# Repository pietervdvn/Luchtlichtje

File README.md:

# Luchtlichtje

Source code and hardware spec of the ESP8266 driven Air Quality Indicator "Luchtlichtje" (Dutch for 'air light')

A small ESP/Arduino Project, showing lights indicating the air quality, based on data from luftdaten.info

## API

Get your sensor data at http://api.luftdaten.info/v1/sensor/7245/

## Bill of Materials

- A Luchtlichtje PCB
- 4 LEDS of each colour (RED, YELLOW, GREEN) of 5mm (or some other colours)
- 3 resistors of around 10ohm (use higher such as 220ohm for less brightness)
- 1 photoresistor of a pretty high resistance, in combination with a 1Mohm resistor*

*If you don't like the brightness settings or have a different photoresistor, you can change the code to have other settings*

## Flashing a Luchtlichtje

- Install platformio
- Open the console
- cd to the desired directory (v0.2/firmware)
- `sudo platformio run --target upload`
- Use `platformio run --target monitor` to see what is happening

## Assembly instructions

- Start with placing the resistors. The resistor 'R1 Different'-resistor (bottom right) takes the 1-mega-ohm resistor
- The other three have 10-ohm resistors (upper and left side).
- Next, place the leds. Be carefull, they have to be oriented correctly: the flattened sides go in the middle. Green leds down, red leds up - just like traffic lights. Solder them neatly and straight.
- Place and solder the header pins on the backside of the board.
- Flash the software on the nodemcu and place it on the backside (see above).
- Gently break the board along the cutlines on the right. If they don't come off, use a knife on the back side of the board.
- These small rectangular break-off pieces can be slided in the main board, to place it on your desk.
- The break-off parts easily fall of the board when lifted. To prevent this, place a piece of wire through the holes in the break-off part and the main board.
- All done! Enjoy your Luchtlichtje.

## Troubleshooting

When booting, the board will test all leds blinking from up to down.
If a led does not blink, check the soldering.
If more then the desired leds burn, some LEDS are soldered in the wrong direction.

If the orange leds start blinking one after another; the board is connecting to the wifi. This will always happen for a few seconds when booting.

If the reds leds are blinking, either luftdaten or your sensor is down. 

## Versions

The first version (v1.0) is dated 2018-05-15
The second version (v2.0) is dated 2018-08-24. Changes are: removal of unused transistors, addition of a brightness sensor, fancier placement of resistors.

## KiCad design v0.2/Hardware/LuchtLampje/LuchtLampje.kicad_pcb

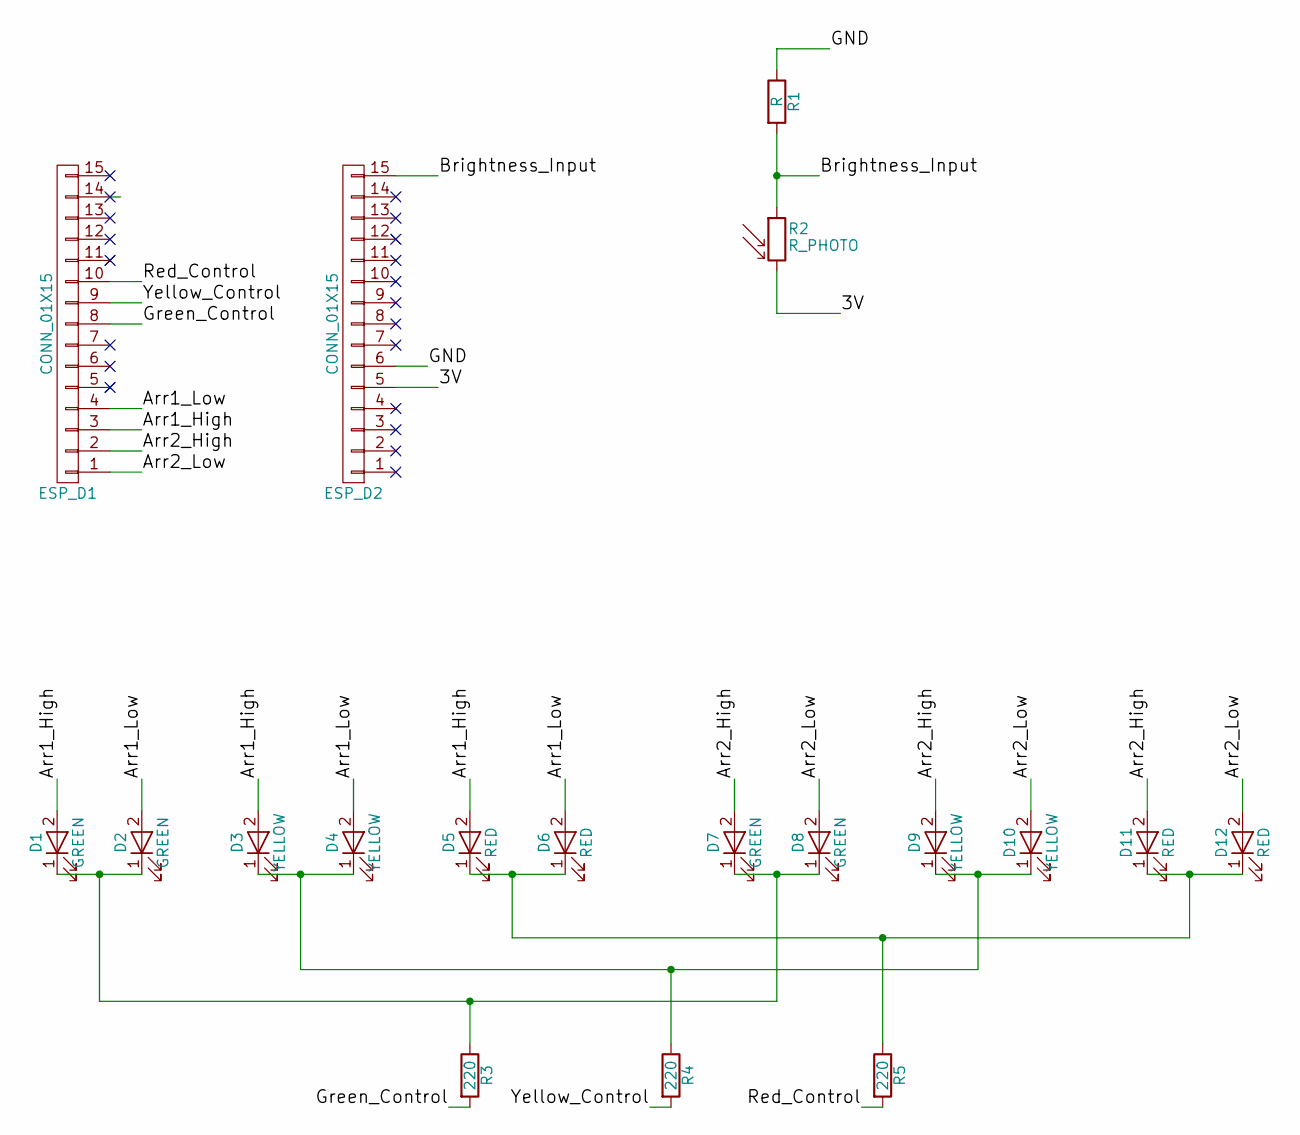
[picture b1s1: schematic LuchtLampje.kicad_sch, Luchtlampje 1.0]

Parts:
D1, D2, D7, D8: GREEN; LED_D5.0mm
D3, D4, D9, D10: YELLOW; LED_D5.0mm
D5, D6, D11, D12: RED; LED_D5.0mm
ESP_D1, ESP_D2: CONN_01X15; Socket_Strip_Straight_1x15_Pitch2.54mm
R1: R; R_Axial_DIN0411_L9.9mm_D3.6mm_P12.70mm_Horizontal
R2: R_PHOTO; R1
R3, R4, R5: 220; R_Axial_DIN0411_L9.9mm_D3.6mm_P12.70mm_Horizontal

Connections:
/3V: ESP_D2.5, R2.2
/Arr1_High: D1.2 (A), D3.2 (A), D5.2 (A), ESP_D1.3
/Arr1_Low: D2.2 (A), D4.2 (A), D6.2 (A), ESP_D1.4
/Arr2_High: D7.2 (A), D9.2 (A), D11.2 (A), ESP_D1.2
/Arr2_Low: D8.2 (A), D10.2 (A), D12.2 (A), ESP_D1.1
/Brightness_Input: ESP_D2.15, R1.2, R2.1
/GND: ESP_D2.6, R1.1
/Green_Control: ESP_D1.8, R3.2
/Red_Control: ESP_D1.10, R5.2
/Yellow_Control: ESP_D1.9, R4.2
unnamed: D1.1 (K), D2.1 (K), D7.1 (K), D8.1 (K), R3.1
unnamed: D3.1 (K), D4.1 (K), D9.1 (K), D10.1 (K), R4.1
unnamed: D5.1 (K), D6.1 (K), D11.1 (K), D12.1 (K), R5.1

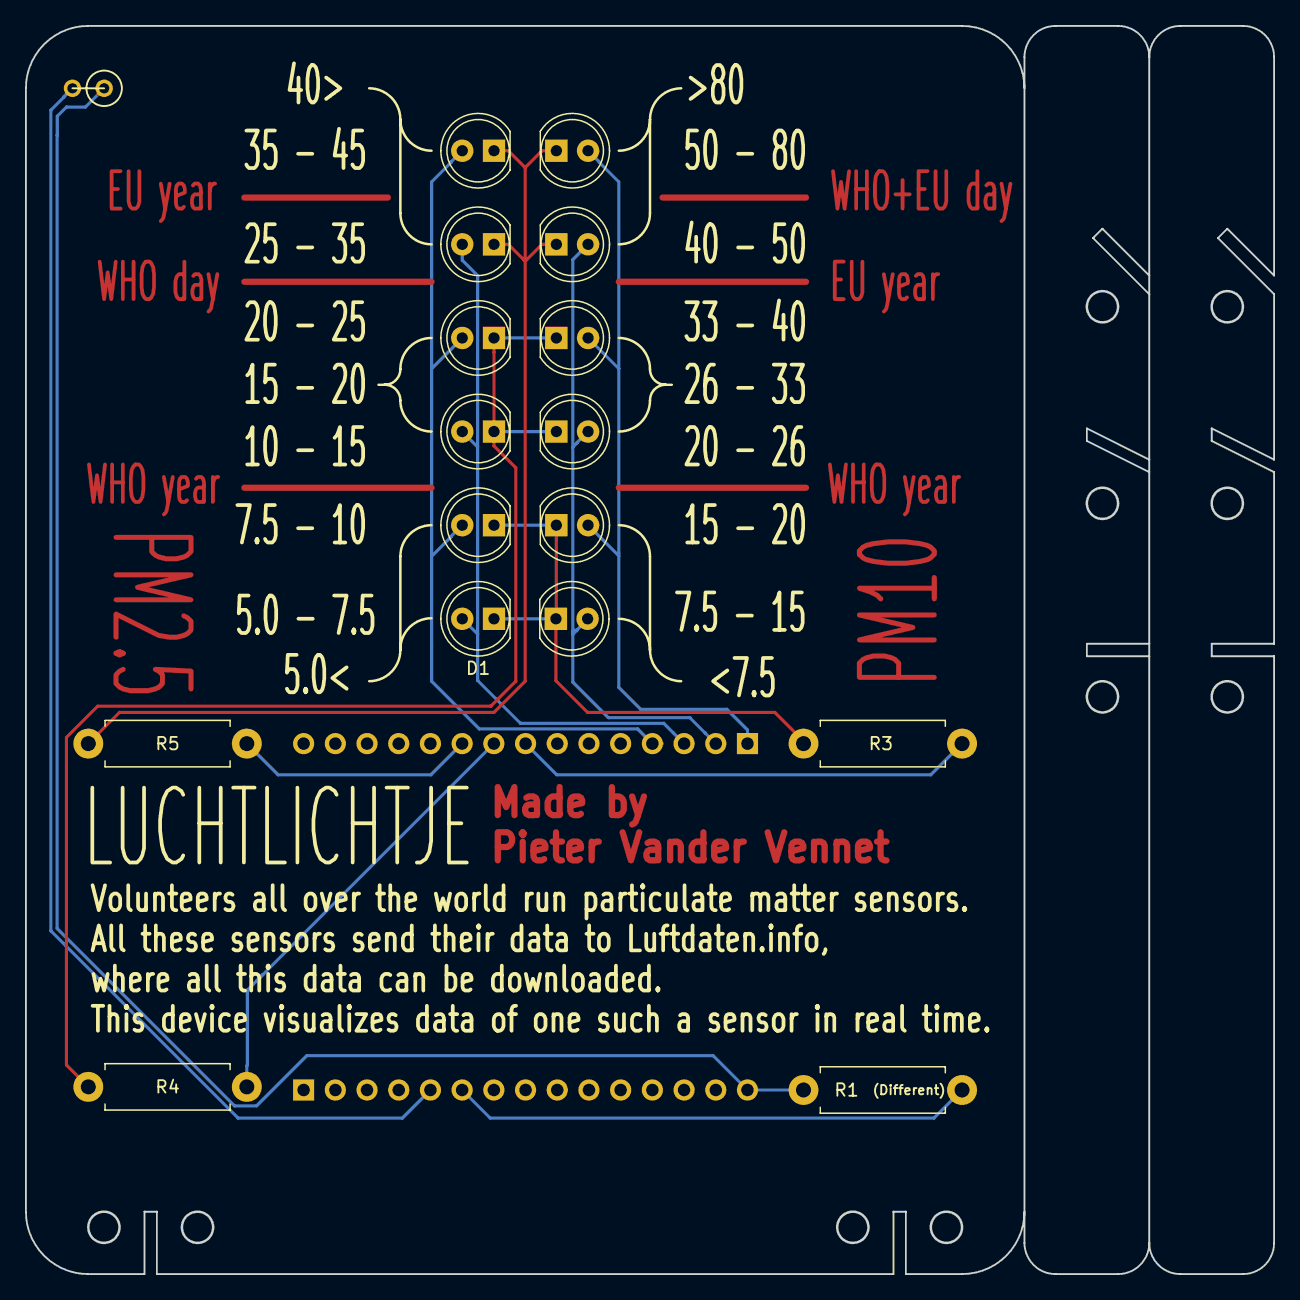
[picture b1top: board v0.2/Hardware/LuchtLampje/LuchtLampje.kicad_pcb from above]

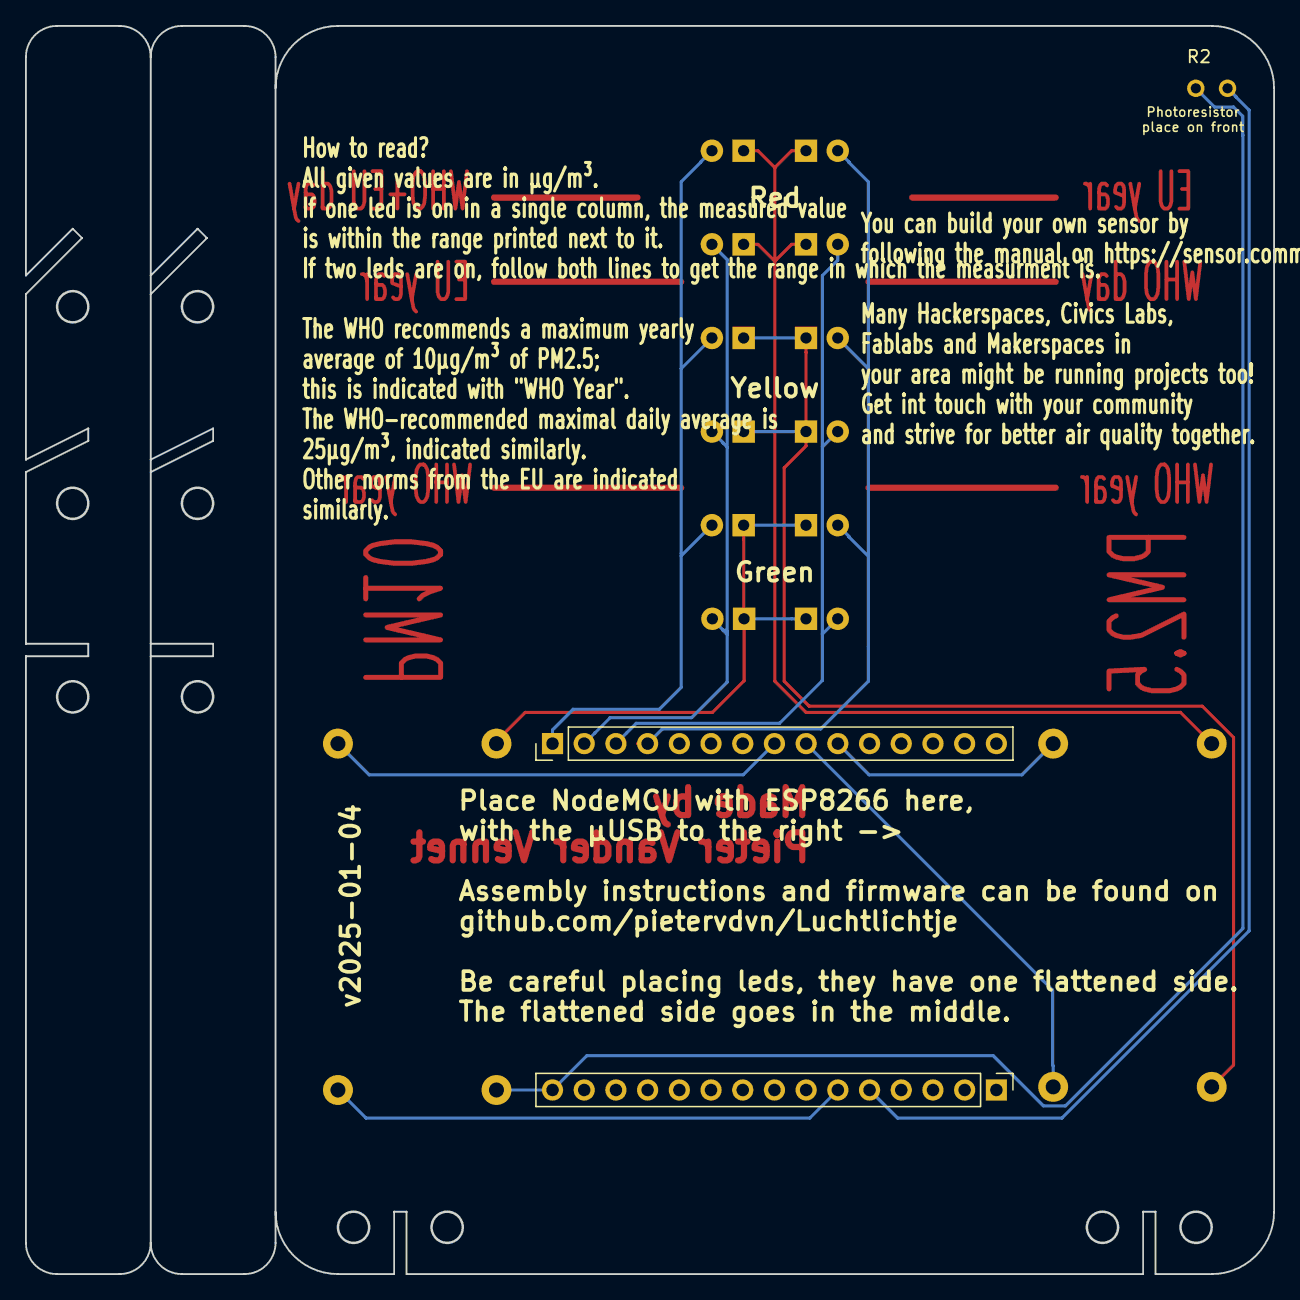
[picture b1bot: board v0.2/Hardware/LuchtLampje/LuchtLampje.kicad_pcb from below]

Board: 2 copper layers, 100.0 x 100.0 mm, 19 parts (2 on the bottom side), 13 nets.

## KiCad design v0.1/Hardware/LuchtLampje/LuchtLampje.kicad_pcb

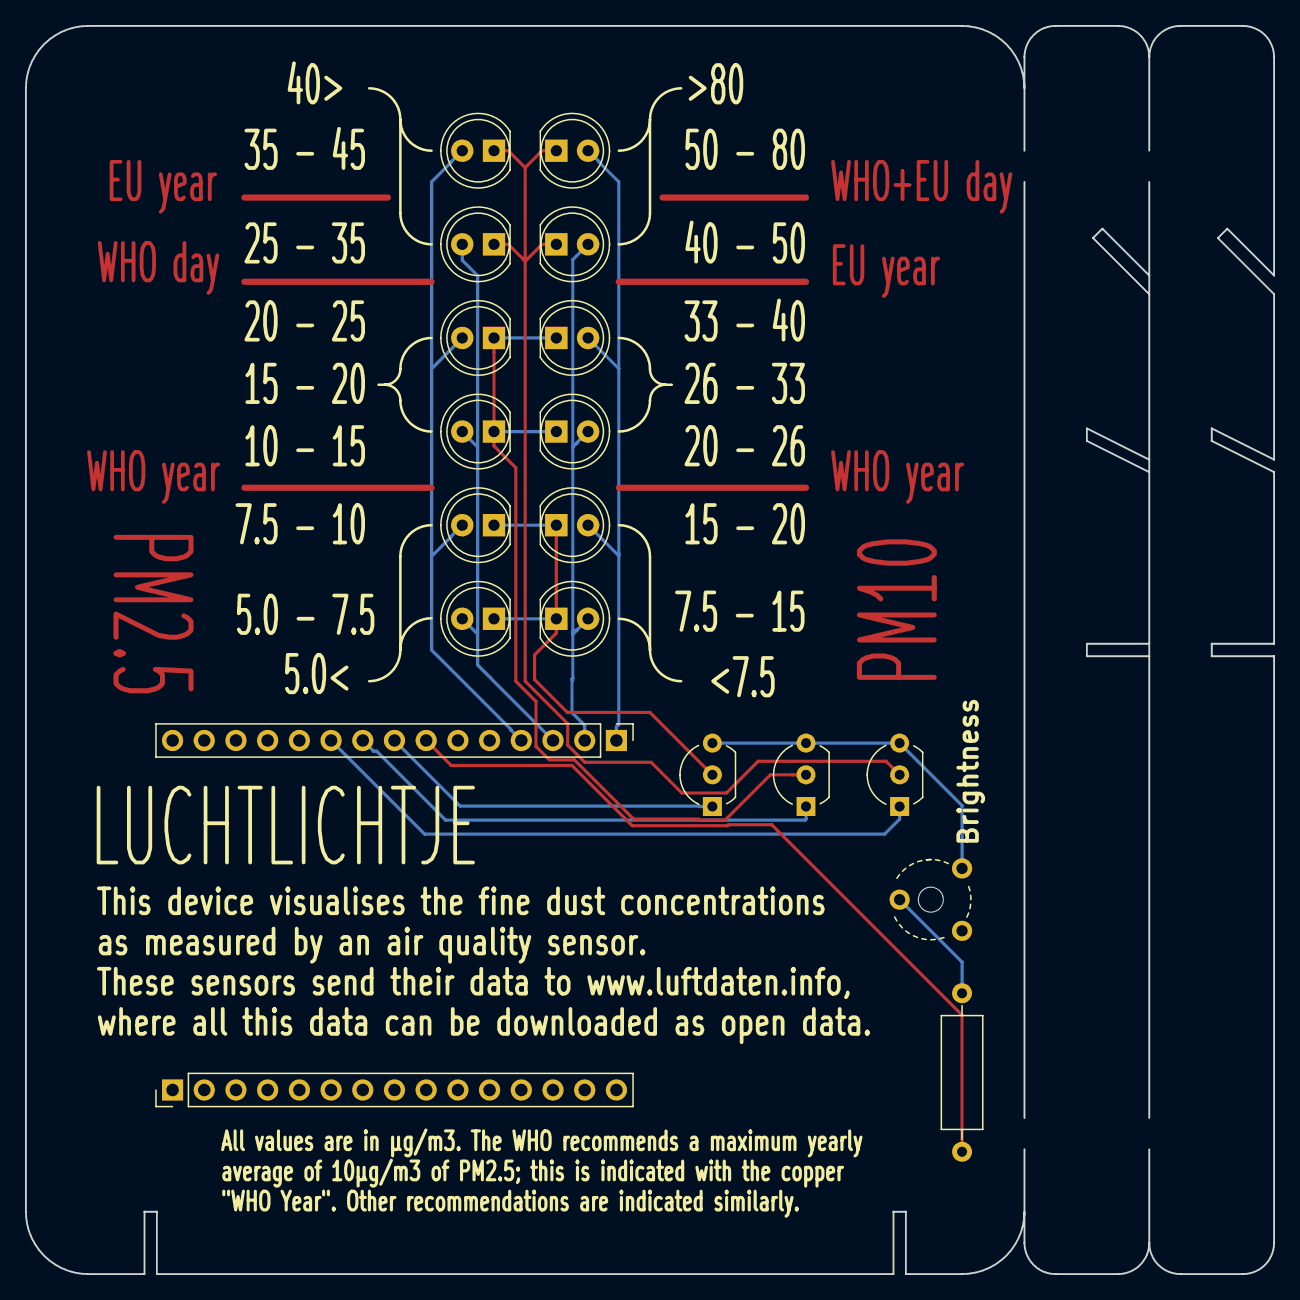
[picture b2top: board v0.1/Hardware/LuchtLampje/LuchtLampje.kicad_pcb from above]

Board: 2 copper layers, 100.0 x 100.0 mm, 19 parts (0 on the bottom side), 13 nets.

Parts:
D2, D7, D8: GREEN; LED_D5.0mm
D3, D4, D9, D10: YELLOW; LED_D5.0mm
D5, D6, D11, D12: RED; LED_D5.0mm
ESP_D1, ESP_D2: CONN_01X15; Socket_Strip_Straight_1x15_Pitch2.54mm
Green: GREEN; LED_D5.0mm
Q1, Q2, Q3: NPN_Green; TO-92_Inline_Wide
R1: 1K; R_Axial_DIN0309_L9.0mm_D3.2mm_P12.70mm_Horizontal
RV1: POT 10K; Potentiometer_Trimmer_Piher_PT-6v_Horizontal_MountLS

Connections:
/Arr1_High: D3.2, D5.2, ESP_D1.3, Green.2
/Arr1_Low: D2.2, D4.2, D6.2, ESP_D1.4
/Arr2_High: D7.2, D9.2, D11.2, ESP_D1.2
/Arr2_Low: D8.2, D10.2, D12.2, ESP_D1.1
/GND: ESP_D1.7, R1.2
/Green_Control: ESP_D1.8, Q1.1
/Red_Control: ESP_D1.10, Q3.1
/Yellow_Control: ESP_D1.9, Q2.1
unnamed: D2.1, D7.1, D8.1, Green.1, Q1.2
unnamed: D3.1, D4.1, D9.1, D10.1, Q2.2
unnamed: D5.1, D6.1, D11.1, D12.1, Q3.2
unnamed: Q1.3, Q2.3, Q3.3, RV1.1
unnamed: R1.1, RV1.2

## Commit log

2018-06-20 Initial code
2018-06-21 Smallest core to get a stable connection
2018-08-19 Temp workspace
2018-08-19 Firmware that should be working if all soldering is correct
2018-08-19 Test code and working code
2018-08-19 Added installation instructions
2018-08-24 Hardware v2.0
2018-09-17 Fixed small typographic issues
2018-09-18 Added brightness controls
2018-09-30 Updated documentation, add binaries
2018-09-30 Added binaries
2019-05-07 Add image
2019-05-07 Add gif
2019-05-07 Images
2019-10-19 Add platformio configuration file.
2019-10-20 Add platformio configuration file for v0.1 firmware.
2019-10-20 Add version information
2019-10-20 Removed v1.0 firmware, add explanation and pointer to v2.0
2019-10-20 Add correct baud rate, remove obsoleted flash script
2019-10-20 Removed compiled version
2019-10-20 Add support for HTTPS, point the device to the new endpoint
2019-10-20 Add platformio instructions, add version information
2019-10-21 Add better handling of values to flatten outliers
2019-11-15 Use WiFiManager for WiFi connectivity instead of hardcoding SSID and password.
2019-11-18 Scripts to flash
2019-11-18 Add quick scripts
2019-12-26 Fix casing of library names. Using the proper name avoids platformio contacting the remote repository for each build.
2020-03-08 Removed fingerprint, use more insecure HTTPS (the S in IOT stands for Security)
2020-03-08 More userfriendlyness, get old config from eeprom
2025-01-04 Update firmware
2025-01-04 Improve landing page
2025-01-04 Small changes
